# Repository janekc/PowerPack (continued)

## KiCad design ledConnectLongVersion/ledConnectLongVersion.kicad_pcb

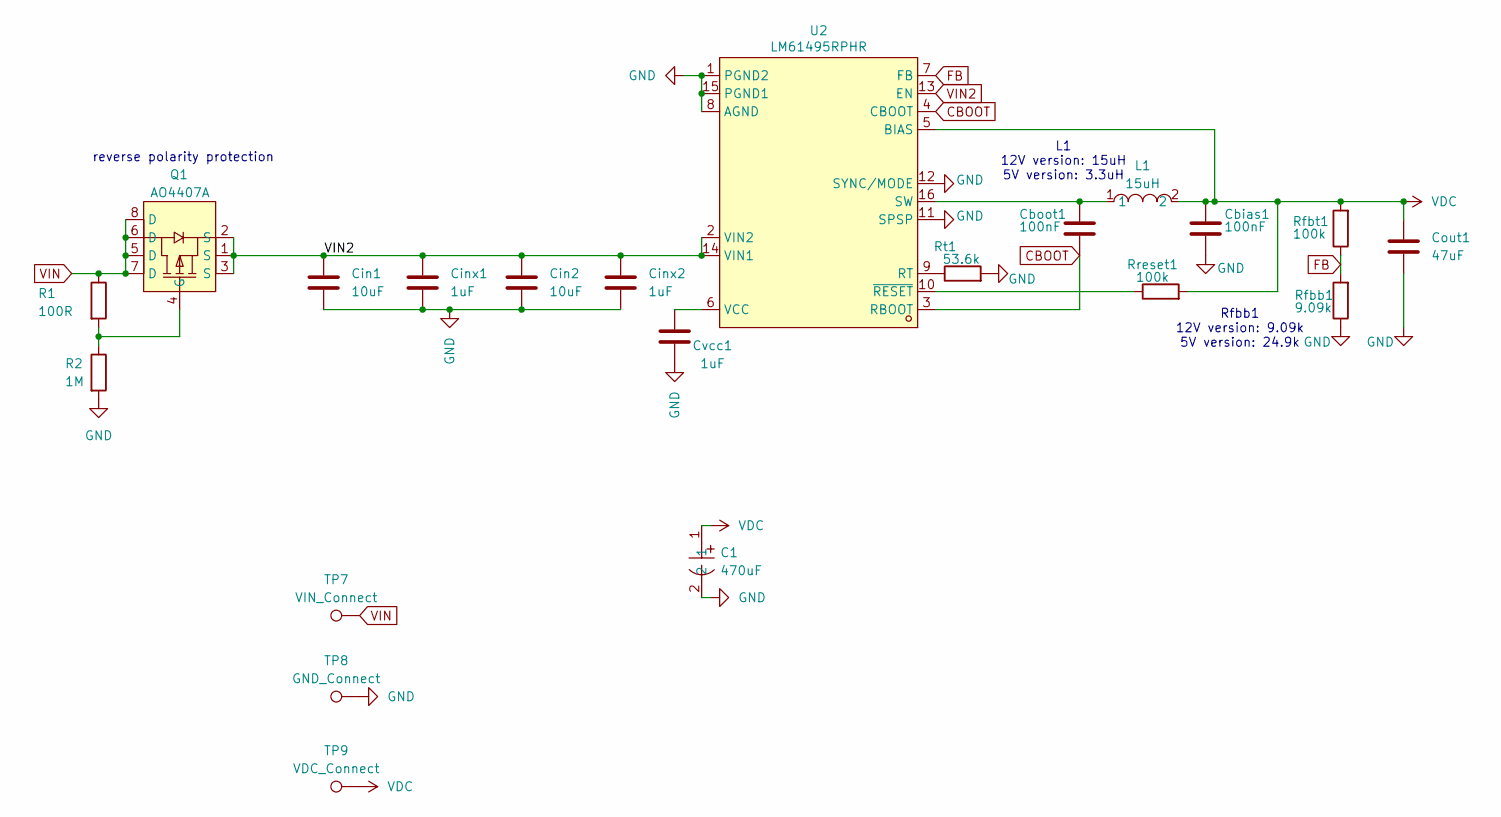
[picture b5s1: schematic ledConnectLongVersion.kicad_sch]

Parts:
C1: 470uF; CAP-TH_BD10.0-P5.00-D0.6-FD; LCSC Part C2688262
Cbias1: 100nF
Cboot1: 100nF; C_0603_1608Metric_Pad1.08x0.95mm_HandSolder
Cin1, Cin2: 10uF; C_0603_1608Metric_Pad1.08x0.95mm_HandSolder
Cinx1, Cinx2: 1uF; C_0603_1608Metric_Pad1.08x0.95mm_HandSolder
Cout1: 47uF; C_1210_3225Metric_Pad1.33x2.70mm_HandSolder
Cvcc1: 1uF; C_0603_1608Metric_Pad1.08x0.95mm_HandSolder
L1: 15uH; IND-SMD_L13.5-W12.6; LCSC Part C2847574
Q1: AO4407A; SOIC-8_L4.9-W3.9-P1.27-LS6.0-BL; LCSC Part C16072
R1: 100R; R_0603_1608Metric_Pad0.98x0.95mm_HandSolder
R2: 1M; R_0603_1608Metric_Pad0.98x0.95mm_HandSolder
Rfbb1: 9.09k; R_0603_1608Metric_Pad0.98x0.95mm_HandSolder
Rfbt1: 100k; R_0603_1608Metric_Pad0.98x0.95mm_HandSolder
Rreset1: 100k; R_0603_1608Metric_Pad0.98x0.95mm_HandSolder
Rt1: 53.6k; R_0603_1608Metric_Pad0.98x0.95mm_HandSolder
TP7: VIN_Connect; TestPoint_Plated_Hole_D3.0mm
TP8: GND_Connect; TestPoint_Plated_Hole_D3.0mm
TP9: VDC_Connect; TestPoint_Plated_Hole_D3.0mm
U2: LM61495RPHR; VQFN-16_L4.5-W3.5-P0.50-TL_TI_RPH; LCSC Part C3198089

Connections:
CBOOT: Cboot1.2, U2.3 (RBOOT), U2.4 (CBOOT)
FB: Rfbb1.2, Rfbt1.1, U2.7 (FB)
GND: C1.2, Cbias1.2, Cin1.2, Cin2.2, Cinx1.2, Cinx2.2, Cout1.2, Cvcc1.2, R2.2, Rfbb1.1, Rt1.2, TP8.1 (1_1), U2.1 (PGND2), U2.8 (AGND), U2.11 (SPSP), U2.12 (SYNC/MODE), U2.15 (PGND1)
unnamed: Q1.4 (G), R1.2, R2.1
unnamed: Rt1.1, U2.9 (RT)
unnamed: Cboot1.1, L1.1, U2.16 (SW)
unnamed: Cvcc1.1, U2.6 (VCC)
unnamed: Rreset1.1, U2.10 (~RESET)
VDC: C1.1, Cbias1.1, Cout1.1, L1.2, Rfbt1.2, Rreset1.2, TP9.1 (1_1), U2.5 (BIAS)
VIN: Q1.5 (D), Q1.6 (D), Q1.7 (D), Q1.8 (D), R1.1, TP7.1 (1_1)
VIN2: Cin1.1, Cin2.1, Cinx1.1, Cinx2.1, Q1.1 (S), Q1.2 (S), Q1.3 (S), U2.2 (VIN2), U2.13 (EN), U2.14 (VIN1)

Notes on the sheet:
Rfbb1 12V version: 9.09k 5V version: 24.9k
L1 12V version: 15uH 5V version: 3.3uH
reverse polarity protection

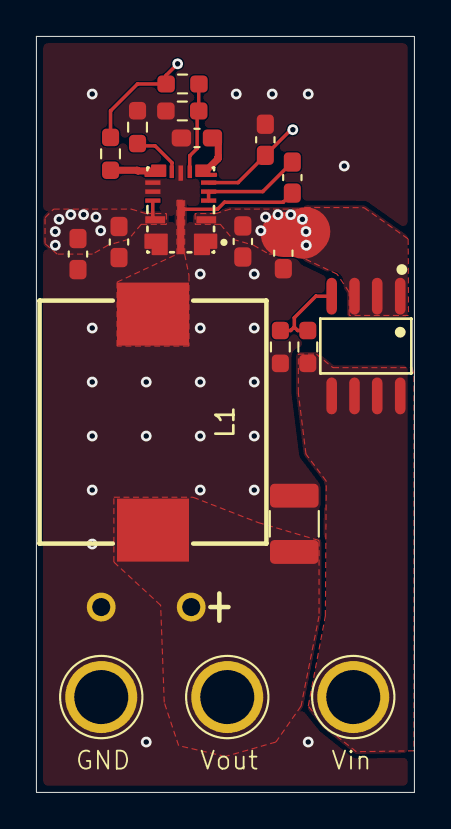
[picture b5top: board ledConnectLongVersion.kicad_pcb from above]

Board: 4 copper layers, 21.0 x 42.0 mm, 21 parts (0 on the bottom side), 11 nets.

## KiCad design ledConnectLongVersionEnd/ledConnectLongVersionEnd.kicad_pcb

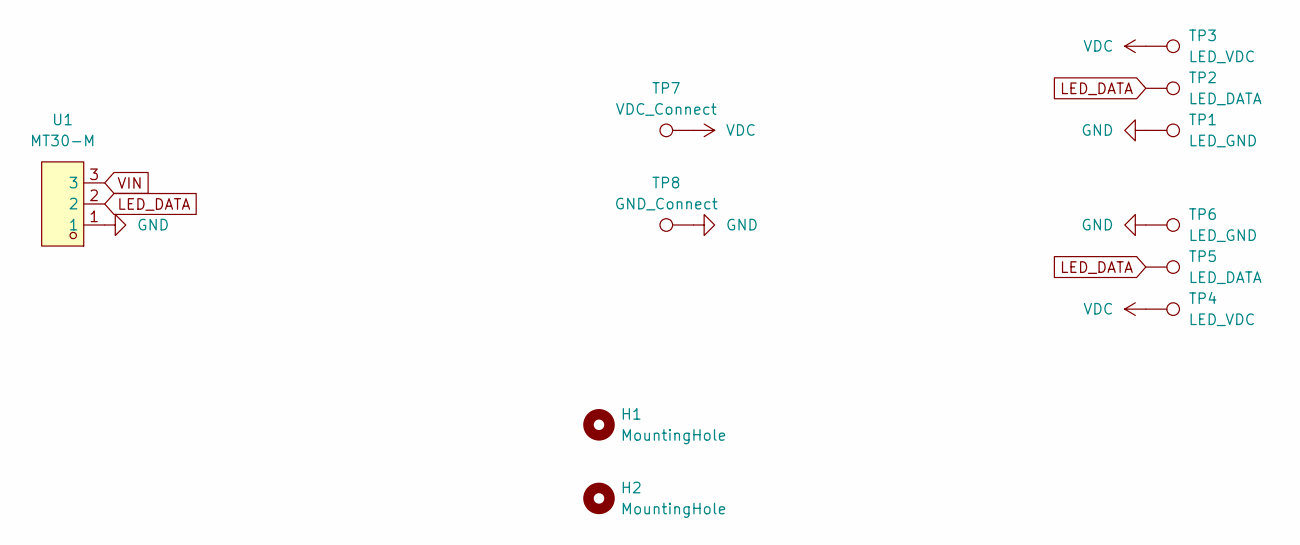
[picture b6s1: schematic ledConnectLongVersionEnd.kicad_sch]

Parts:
H1, H2: MountingHole; MountingHole_2.1mm
TP1, TP6: LED_GND; TestPoint_Pad_2.5x2.5mm
TP2, TP5: LED_DATA; TestPoint_Pad_2.5x2.5mm
TP3, TP4: LED_VDC; TestPoint_Pad_2.5x2.5mm
TP7: VDC_Connect; TestPoint_Plated_Hole_D3.0mm
TP8: GND_Connect; TestPoint_Plated_Hole_D3.0mm
U1: MT30-M; CONN-TH_MT30-M; LCSC Part C99903

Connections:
GND: TP1.1 (1_1), TP6.1 (1_1), TP8.1 (1_1), U1.1
LED_DATA: TP2.1 (1_1), TP5.1 (1_1), U1.2
VDC: TP3.1 (1_1), TP4.1 (1_1), TP7.1 (1_1)
VIN: U1.3

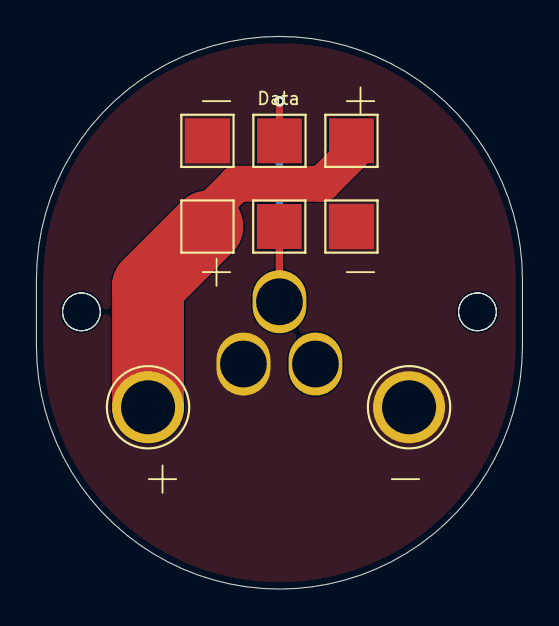
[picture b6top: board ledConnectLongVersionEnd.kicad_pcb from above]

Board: 2 copper layers, 27.0 x 30.7 mm, 13 parts (1 on the bottom side), 3 nets.

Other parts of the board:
H1#2: MountingHole; MountingHole_2.1mm
H2#2: MountingHole_2.1mm

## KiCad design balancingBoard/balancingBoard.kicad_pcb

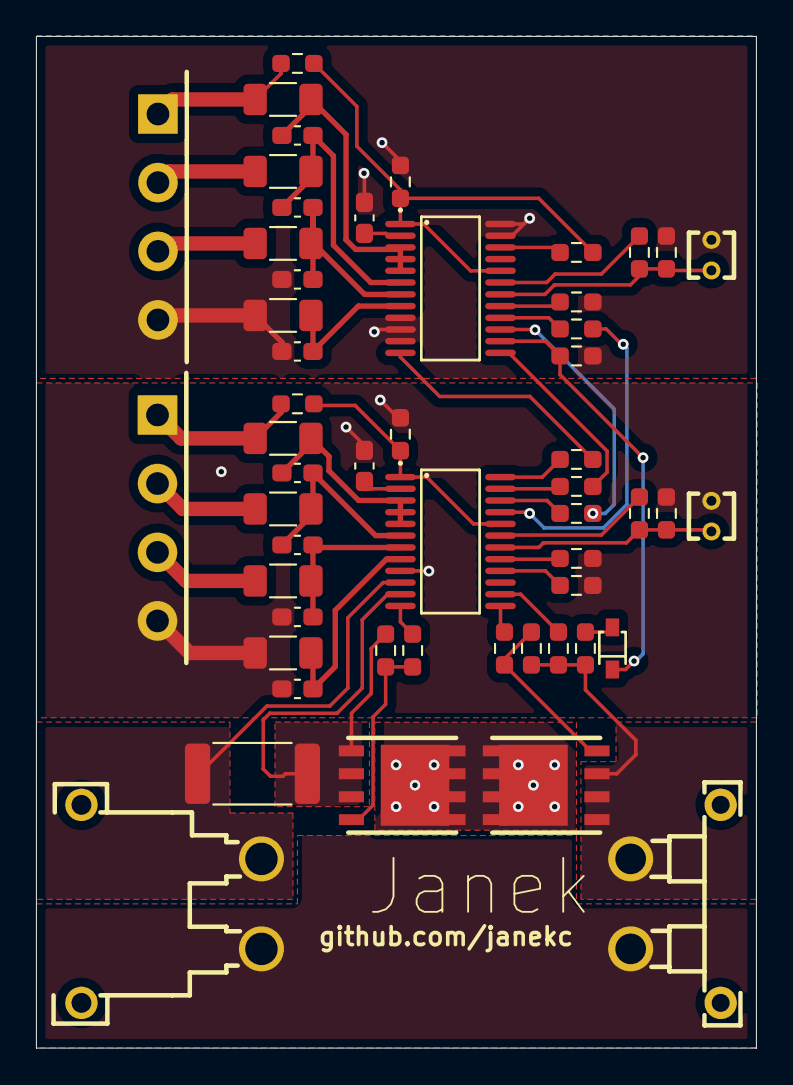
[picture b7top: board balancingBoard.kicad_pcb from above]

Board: 2 copper layers, 40.0 x 56.2 mm, 53 parts (0 on the bottom side), 47 nets.

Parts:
C1, C2, C3, C4, C49, C50, C51, C62: 100nF; C_0603_1608Metric_Pad1.08x0.95mm_HandSolder
C5, C52: 1uF; R_0603_1608Metric_Pad0.98x0.95mm_HandSolder
C6, C53: 1uF; C_0603_1608Metric_Pad1.08x0.95mm_HandSolder
CN1, CN2: WJ15EDGRC-3.81-4P; CONN-TH_WJ15EDGRC-3.81-4P
CN3: XT30PW-M; CONN-TH_XT30PW-M
D2: 1SS355; SOD-323_L1.8-W1.3-LS2.5-RD
Q1, Q3: IRFH5302TRPBF; PQFN-8_L6.0-W5.0-P1.27-LS6.0-BL
R1, R33, R36: 1k; R_0603_1608Metric_Pad0.98x0.95mm_HandSolder
R2, R3, R4, R5, R26, R27, R28, R46: 75; R_1206_3216Metric_Pad1.30x1.75mm_HandSolder
R6, R7, R11: 10M; R_0603_1608Metric_Pad0.98x0.95mm_HandSolder
R8, R9, R10, R12, R17, R18, R21, R48: 10k; R_0603_1608Metric_Pad0.98x0.95mm_HandSolder
R13: 5m; R_2512_6332Metric_Pad1.40x3.35mm_HandSolder
R14, R34: 450k; R_0603_1608Metric_Pad0.98x0.95mm_HandSolder
R15, R19: 103AT-4-050; RES-TH_L2.5-W2.5-P1.70-D0.3
R16, R30, R31: 1M; R_0603_1608Metric_Pad0.98x0.95mm_HandSolder
R32: 4.5k; R_0603_1608Metric_Pad0.98x0.95mm_HandSolder
R47: 100k; R_0603_1608Metric_Pad0.98x0.95mm_HandSolder
U1, U2: BQ7791502PWR; TSSOP-24_L7.8-W4.4-P0.65-LS6.4-BL_1
U3: XT30PW-F; CONN-TH_XT30PW-F-1

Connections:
-BATT: CN3.1 (-), R13.1, U1.10 (SRP)
BCBO: R12.2, U1.21 (CBO)
BPRES: R8.2, U1.22 (PRES)
CTRC: R6.2, U1.23 (CTRC)
CTRD: R7.1, U1.24 (CTRD)
GND: C51.1, C52.1, C53.1, C62.2, CN2.4, R18.2, R19.2, R46.1, R47.1, R48.1, U1.9 (VSS)
unnamed: CN1.1, R1.1, R2.1
unnamed: CN1.2, R3.1
unnamed: CN1.3, R4.1
unnamed: CN2.2, R27.1
unnamed: CN2.3, R28.1
unnamed: D2.2 (A), R14.1
unnamed: D2.1 (C), R16.1, U2.14 (LD)
unnamed: Q1.5 (D), Q1.6 (D), Q1.7 (D), Q1.8 (D), Q1.9 (D), Q3.5 (D), Q3.6 (D), Q3.7 (D), Q3.8 (D), Q3.9 (D)
unnamed: Q1.4 (G), R30.1, R32.2
unnamed: Q3.4 (G), R31.1, R33.2
unnamed: C53.2, U1.2 (AVDD)
unnamed: R48.2, U1.16 (CBI)
unnamed: C52.2, R36.2, U1.1 (VDD), U1.20 (CCFG)
unnamed: R33.1, U1.13 (CHG)
unnamed: R32.1, U1.12 (DSG)
unnamed: R34.1, U1.14 (LD)
unnamed: R47.2, U1.17 (OCDP)
unnamed: Q1.1 (S), Q1.2 (S), Q1.3 (S), R13.2, R30.2, U1.11 (SRN)
unnamed: R18.1, R19.1, R21.2, U1.18 (TS)
unnamed: C50.2, C62.1, R28.2, U1.7 (VC1)
unnamed: C49.2, C50.1, R27.2, U1.6 (VC2)
unnamed: C49.1, R26.2, U1.3 (VC5), U1.4 (VC4), U1.5 (VC3)
unnamed: C51.2, R46.2, U1.8 (VCO)
unnamed: R21.1, U1.19 (VTB)
unnamed: C6.2, U2.2 (AVDD)
unnamed: R12.1, U2.16 (CBI)
unnamed: C5.2, R1.2, R9.2, U2.1 (VDD), U2.20 (CCFG)
unnamed: R6.1, U2.13 (CHG)
unnamed: C3.2, C4.1, C5.1, C6.1, CN1.4, CN2.1, R5.1, R11.1, R15.2, R16.2, R17.2, R26.1, R36.1, U2.9 (VSS), U2.10 (SRP), U2.11 (SRN), U2.23 (CTRC), U2.24 (CTRD)
unnamed: R7.2, U2.12 (DSG)
unnamed: R8.1, U2.15 (LPWR)
unnamed: R11.2, U2.17 (OCDP)
unnamed: R9.1, U2.22 (PRES)
unnamed: R10.2, R15.1, R17.1, U2.18 (TS)
unnamed: C1.2, C3.1, R4.2, U2.7 (VC1)
unnamed: C1.1, C2.2, R3.2, U2.6 (VC2)
unnamed: C2.1, R2.2, U2.3 (VC5), U2.4 (VC4), U2.5 (VC3)
unnamed: C4.2, R5.2, U2.8 (VCO)
unnamed: R10.1, U2.19 (VTB)
PACK+: CN3.2 (+), U3.1
PACK-: Q3.1 (S), Q3.2 (S), Q3.3 (S), R14.2, R31.2, R34.2, U3.2

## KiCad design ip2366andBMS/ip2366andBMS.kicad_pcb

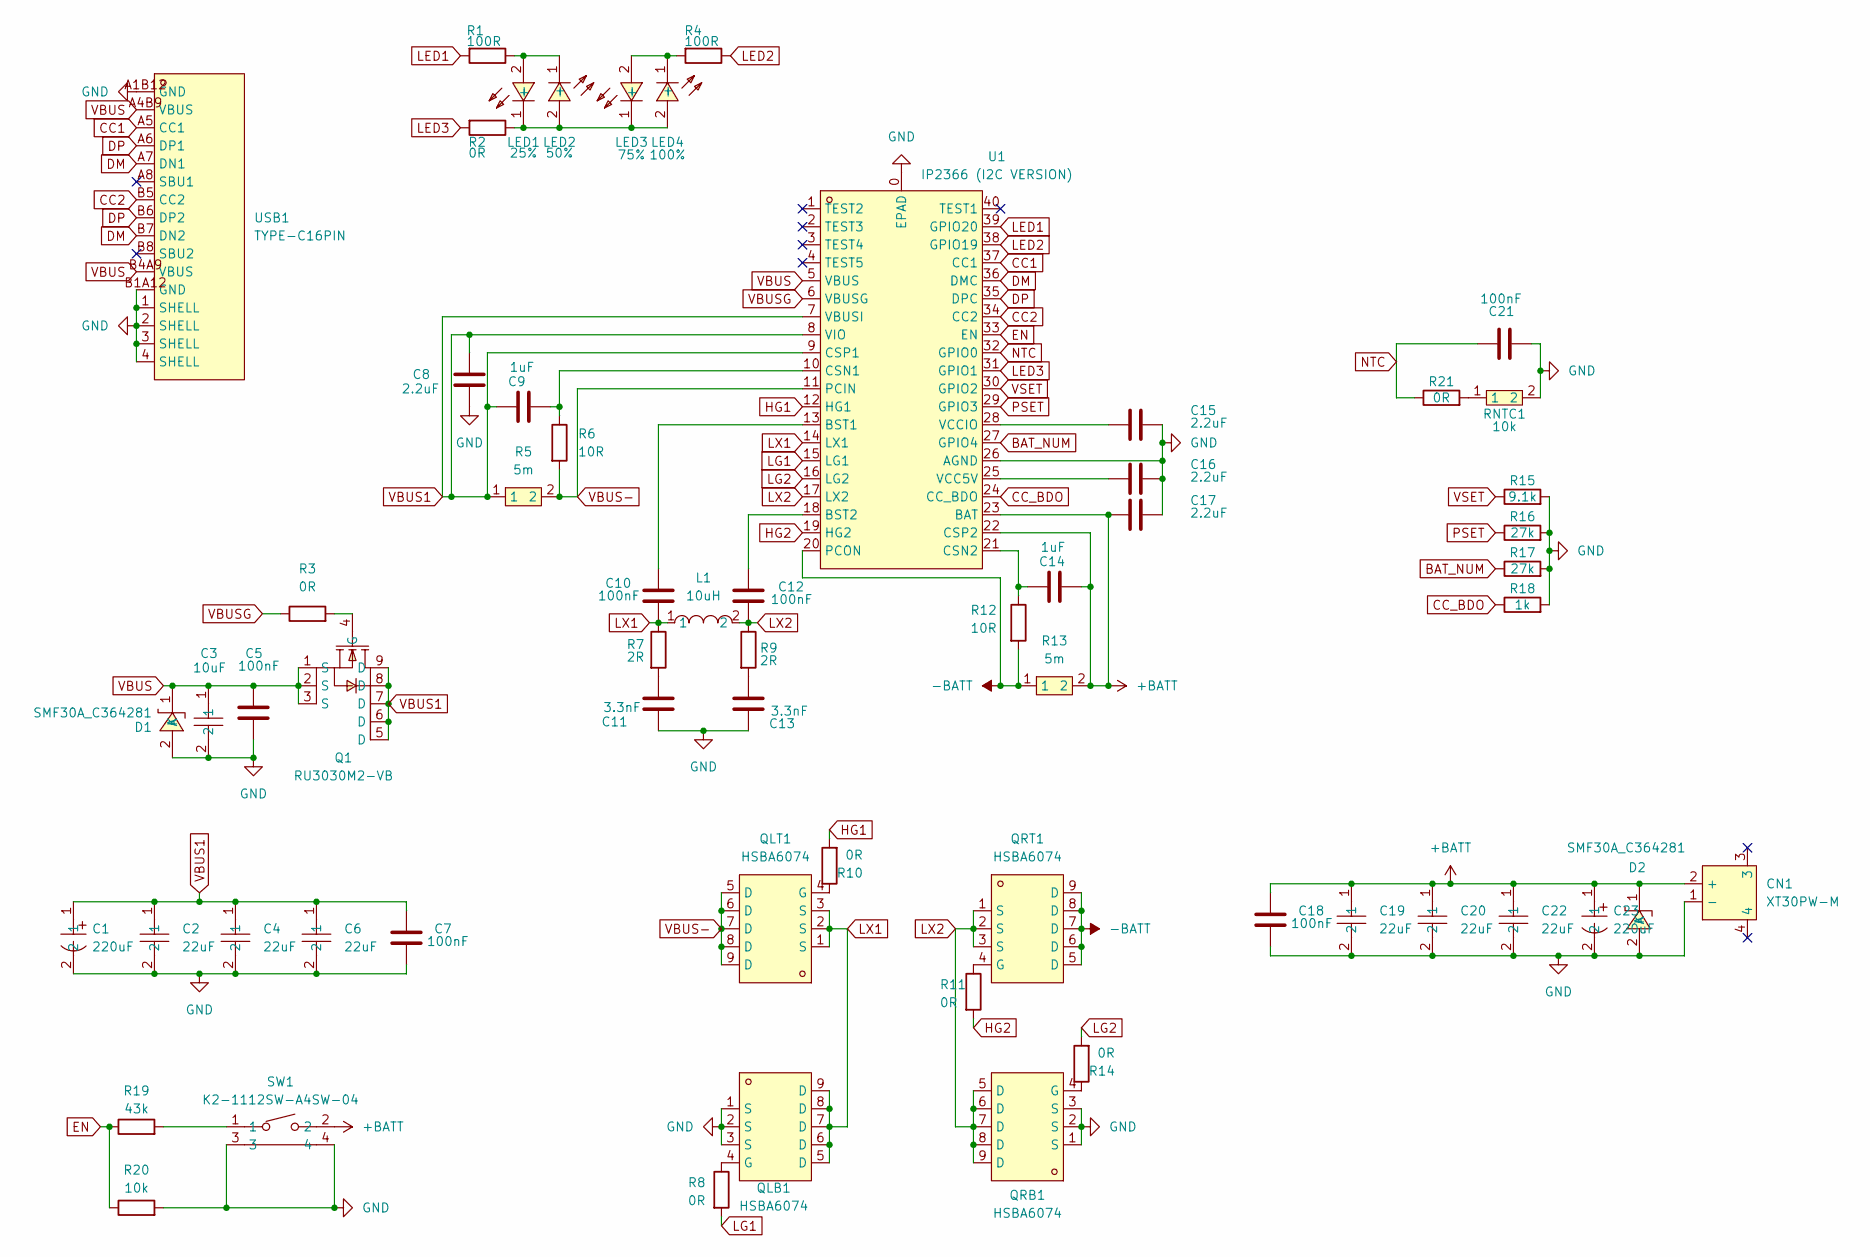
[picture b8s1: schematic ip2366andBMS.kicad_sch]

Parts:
C1, C23: 220uF; CAP-TH_BD8.0-P3.50-D0.6-FD; LCSC Part C2688260
C2, C4, C6, C19, C20, C22: 22uF; C1210; LCSC Part C778721
C3: 10uF; C1206; LCSC Part C89632
C5, C7, C10, C12, C18, C21: 100nF; C_0603_1608Metric_Pad1.08x0.95mm_HandSolder
C8, C15, C16, C17: 2.2uF; C_0603_1608Metric_Pad1.08x0.95mm_HandSolder
C9, C14: 1uF; C_0603_1608Metric_Pad1.08x0.95mm_HandSolder
C11, C13: 3.3nF; C_0603_1608Metric_Pad1.08x0.95mm_HandSolder
CN1: XT30PW-M; CONN-TH_XT30PW-M; LCSC Part C431092
D1, D2: SMF30A_C364281; SOD-123_L2.6-W1.6-LS3.5-RD; LCSC Part C364281
L1: 10uH; IND-SMD_L13.5-W12.5; LCSC Part C840531
LED1: 25%; LED0603-RD; LCSC Part C84265
LED2: 50%; LED0603-RD; LCSC Part C84265
LED3: 75%; LED0603-RD; LCSC Part C84265
LED4: 100%; LED0603-RD; LCSC Part C84265
Q1: RU3030M2-VB; DFN-8_L3.0-W3.0-P0.65-BL_VBQFXXXX; LCSC Part C19190164
QLB1: HSBA6074; DFN-8_L5.7-W5.1-P1.27-LS6.1-BL-2; LCSC Part C2903566
QLT1: HSBA6074; DFN-8_L5.7-W5.1-P1.27-LS6.1-BL-2; LCSC Part C2903566
QRB1: HSBA6074; DFN-8_L5.7-W5.1-P1.27-LS6.1-BL-2; LCSC Part C2903566
QRT1: HSBA6074; DFN-8_L5.7-W5.1-P1.27-LS6.1-BL-2; LCSC Part C2903566
R1, R4: 100R; R_0603_1608Metric_Pad0.98x0.95mm_HandSolder
R2, R3, R8, R10, R11, R14, R21: 0R; R_0603_1608Metric_Pad0.98x0.95mm_HandSolder
R5, R13: 5m; R_2512_6332Metric_Pad1.40x3.35mm_HandSolder; LCSC Part C5123656
R6: 10R; R_0603_1608Metric_Pad0.98x0.95mm_HandSolder
R7, R9: 2R; R_0603_1608Metric_Pad0.98x0.95mm_HandSolder
R12: 10R; C_0603_1608Metric_Pad1.08x0.95mm_HandSolder
R15: 9.1k; R_0603_1608Metric_Pad0.98x0.95mm_HandSolder
R16, R17: 27k; R_0603_1608Metric_Pad0.98x0.95mm_HandSolder
R18: 1k; R_0603_1608Metric_Pad0.98x0.95mm_HandSolder
R19: 43k; R_0603_1608Metric_Pad0.98x0.95mm_HandSolder
R20: 10k; R_0603_1608Metric_Pad0.98x0.95mm_HandSolder
RNTC1: 10k; R0603; LCSC Part C98220
SW1: K2-1112SW-A4SW-04; KEY-TH_K2-1112SW-AXXW-XX; LCSC Part C223811
U1: IP2366 (I2C VERSION); QFN-40_L5.0-W5.0-P0.40-TL-EP3.7; LCSC Part C20415848
USB1: TYPE-C16PIN; USB-C-SMD_TYPE-C16PIN; LCSC Part C393939

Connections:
+BATT: C14.1, C17.2, C18.1, C19.1, C20.1, C22.1, C23.1, CN1.2 (+), D2.1 (K), R13.2, SW1.2, U1.22 (CSP2), U1.23 (BAT)
-BATT: QRT1.5 (D), QRT1.6 (D), QRT1.7 (D), QRT1.8 (D), QRT1.9 (D), R12.2, R13.1, U1.20 (PCON)
BAT_NUM: R17.1, U1.27 (GPIO4)
CC1: U1.37 (CC1), USB1.A5 (CC1)
CC2: U1.34 (CC2), USB1.B5 (CC2)
CC_BDO: R18.1, U1.24 (CC_BDO)
DM: U1.36 (DMC), USB1.A7 (DN1), USB1.B7 (DN2)
DP: U1.35 (DPC), USB1.A6 (DP1), USB1.B6 (DP2)
EN: R19.1, R20.1, U1.33 (EN)
GND: C1.2, C2.2, C3.2, C4.2, C5.2, C6.2, C7.2, C8.2, C11.2, C13.2, C15.1, C16.1, C17.1, C18.2, C19.2, C20.2, C21.2, C22.2, C23.2, CN1.1 (-), D1.2 (A), D2.2 (A), QLB1.1 (S), QLB1.2 (S), QLB1.3 (S), QRB1.1 (S), QRB1.2 (S), QRB1.3 (S), R15.2, R16.2, R17.2, R18.2, R20.2, RNTC1.2, SW1.3, SW1.4, U1.0 (EPAD), U1.26 (AGND), USB1.1 (SHELL), USB1.2 (SHELL), USB1.3 (SHELL), USB1.4 (SHELL), USB1.A1B12 (GND), USB1.B1A12 (GND)
HG1: R10.2, U1.12 (HG1)
HG2: R11.2, U1.19 (HG2)
LED1: R1.2, U1.39 (GPIO20)
LED2: R4.1, U1.38 (GPIO19)
LED3: R2.2, U1.31 (GPIO1)
LG1: R8.2, U1.15 (LG1)
LG2: R14.2, U1.16 (LG2)
LX1: C10.2, L1.1, QLB1.5 (D), QLB1.6 (D), QLB1.7 (D), QLB1.8 (D), QLB1.9 (D), QLT1.1 (S), QLT1.2 (S), QLT1.3 (S), R7.1, U1.14 (LX1)
LX2: C12.2, L1.2, QRB1.5 (D), QRB1.6 (D), QRB1.7 (D), QRB1.8 (D), QRB1.9 (D), QRT1.1 (S), QRT1.2 (S), QRT1.3 (S), R9.1, U1.17 (LX2)
NTC: C21.1, R21.1, U1.32 (GPIO0)
unnamed: C11.1, R7.2
unnamed: C13.1, R9.2
unnamed: LED1.2 (+), LED2.1 (-), R1.1
unnamed: LED1.1 (-), LED2.2 (+), LED3.1 (-), LED4.2 (+), R2.1
unnamed: LED3.2 (+), LED4.1 (-), R4.2
unnamed: Q1.4 (G), R3.2
unnamed: QLB1.4 (G), R8.1
unnamed: QLT1.4 (G), R10.1
unnamed: QRB1.4 (G), R14.1
unnamed: QRT1.4 (G), R11.1
unnamed: R19.2, SW1.1
unnamed: R21.2, RNTC1.1
unnamed: C10.1, U1.13 (BST1)
unnamed: C12.1, U1.18 (BST2)
unnamed: C9.1, R6.1, U1.10 (CSN1)
unnamed: C14.2, R12.1, U1.21 (CSN2)
unnamed: C16.2, U1.25 (VCC5V)
unnamed: C15.2, U1.28 (VCCIO)
PSET: R16.1, U1.29 (GPIO3)
VBUS: C3.1, C5.1, D1.1 (K), Q1.1 (S), Q1.2 (S), Q1.3 (S), U1.5 (VBUS), USB1.A4B9 (VBUS), USB1.B4A9 (VBUS)
VBUS1: C1.1, C2.1, C4.1, C6.1, C7.1, C8.1, C9.2, Q1.5 (D), Q1.6 (D), Q1.7 (D), Q1.8 (D), Q1.9 (D), R5.1, U1.7 (VBUSI), U1.8 (VIO), U1.9 (CSP1)
VBUS-: QLT1.5 (D), QLT1.6 (D), QLT1.7 (D), QLT1.8 (D), QLT1.9 (D), R5.2, R6.2, U1.11 (PCIN)
VBUSG: R3.1, U1.6 (VBUSG)
VSET: R15.1, U1.30 (GPIO2)

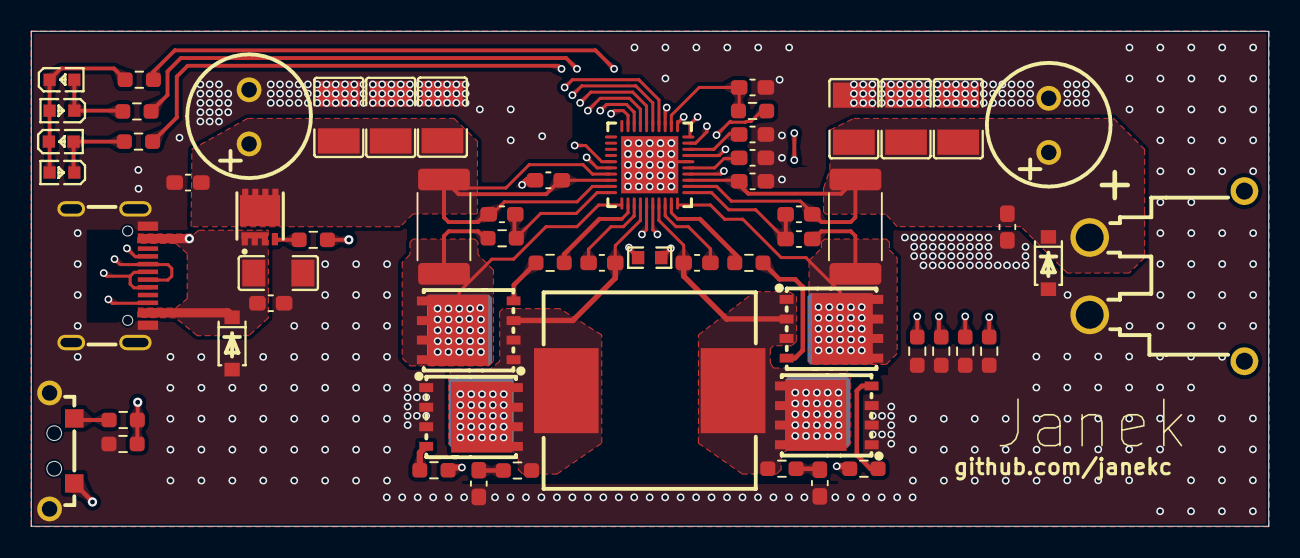
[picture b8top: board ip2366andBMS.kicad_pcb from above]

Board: 4 copper layers, 80.0 x 32.0 mm, 61 parts (0 on the bottom side), 44 nets.

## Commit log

2025-11-17 init
2025-11-18 start pcb design
2025-11-18 route pcb
2025-11-19 fix usbc connector
2025-11-20 start new board design based on the ip2366
2025-11-21 add some components
2025-11-21 add some more components
2025-11-24 add balancing board
2025-11-24 replace the inductor
2025-12-04 update#
2025-12-04 add layout for balancingboard
2025-12-05 aktueller stand
2025-12-05 add teardrops
2025-12-05 add fabrication outputs
2025-12-08 stand
2025-12-09 add layout
2025-12-09 next board
2025-12-10 testownbucklayout
2025-12-10 via stiching fehlt noch
2025-12-11 save everything
2025-12-12 base balancing byd
2025-12-12 next step
2025-12-12 balancing board route
2025-12-13 bestelle teile
2025-12-14 ordered parts
2025-12-14 add logo
2025-12-14 kurz vor bestellung
2025-12-14 bestellt
2025-12-21 generate all boms
2025-12-21 rename and regen boms
2025-12-21 add kicanvas viewer
2025-12-21 update kicanvas boards
2026-01-13 add some more
2026-03-28 new routing for ledbrain
2026-03-30 update lcsc bestellt
2026-03-30 wladqjieu
2026-04-04 these his
2026-04-10 update stuff a little bit
2026-04-10 lsdk
2026-04-11 more
